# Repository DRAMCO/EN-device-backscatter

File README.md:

## Firmware

The firmware **firmware-vscode-exp-4b-part-2** is used in [experiment 4b](https://github.com/techtile-by-dramco/experiments/tree/main/04_backscatter_communication) part 2.

The firmware [**firmware-vscode-exp-4b-part-2-pseudorandom**](https://github.com/techtile-by-dramco/EN-device-backscatter/tree/main/firmware-vscode-exp-4b-part-2-pseudorandom) transmits 10 bytes preamble (0xAA) + 4096 bytes pseudo random code (baudrate 1000 bps) with a delay of 5 seconds between each transmission cycle.
One cycle requires 8 [bits/byte] * 1 [ms/bit] * (10 + 4096) [bytes] or in total 32.848 seconds.

## GNU Radio

The folder `gnuradio` contains the RX and TX files. The `receiver` folder contains `OOK.grc` to demodulate the modulated backscatter signal.

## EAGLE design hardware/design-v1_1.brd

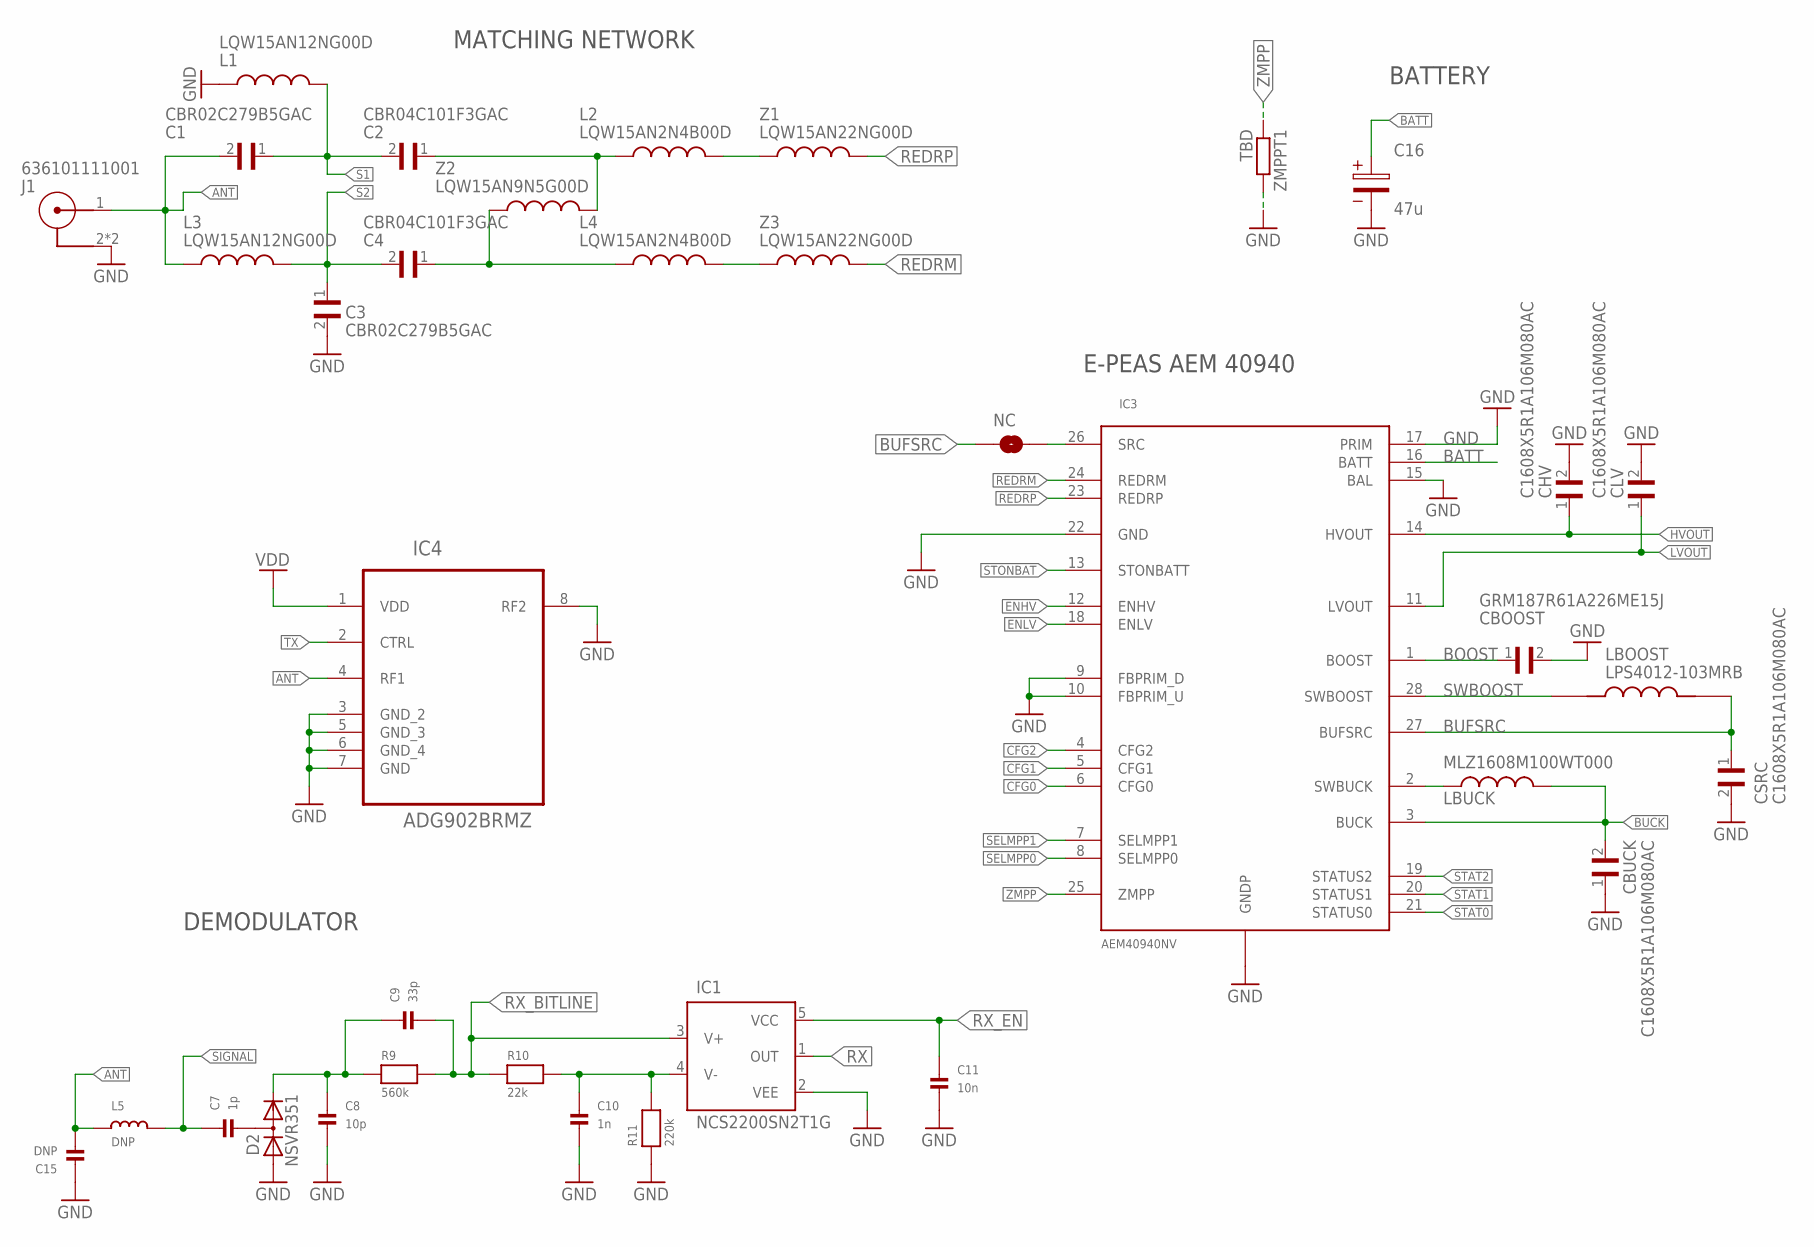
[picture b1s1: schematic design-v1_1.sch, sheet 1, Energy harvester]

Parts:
C1, C3: CBR02C279B5GAC; CAPC1005X55N
C2, C4: CBR04C101F3GAC; CAPC1005X55N
C7: 1p; 0402
C8: 10p; 0402
C9: 33p; 0402
C10: 1n; 0402
C11: 10n; 0402
C15: DNP; 0402
C16: 47u; 3X1.6X1.4(BXCXA)
CBOOST: GRM187R61A226ME15J; CAPC1608X80N
CBUCK: C1608X5R1A106M080AC; CAPC1608X90N
CHV: C1608X5R1A106M080AC; CAPC1608X90N
CLV: C1608X5R1A106M080AC; CAPC1608X90N
CSRC: C1608X5R1A106M080AC; CAPC1608X90N
D2: NSVR351; SOT23
IC1: NCS2200SN2T1G; SOT95P275X110-5N
IC3: AEM40940NV; QFN28_5X5_05P_NO_VIAS
IC4: ADG902BRMZ; SOP65P490X110-8N
J1: 636101111001
L1, L3: LQW15AN12NG00D; INDC1006X60N
L2, L4: LQW15AN2N4B00D; INDC1006X60N
L5: DNP; _0402
LBOOST: LPS4012-103MRB; IND_LPS4012-103MRB
LBUCK: MLZ1608M100WT000; INDC1608X95N
NC: JUMPER-SMT_2_NO_SILK; SMT-JUMPER_2_NO_SILK
R9: 560k; 0402
R10: 22k; 0402
R11: 220k; 0402
Z1, Z3: LQW15AN22NG00D; INDC1006X60N
Z2: LQW15AN9N5G00D; INDC1006X60N
ZMPPT1: TBD; R0805

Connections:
ANT: C1.2, C15.2, IC4.4 (RF1), J1.1, L3.1, L5.1
BATT: C16.1, IC3.16 (BATT); also elsewhere on the board
BOOST: CBOOST.1, IC3.1 (BOOST); also elsewhere on the board
BUCK: CBUCK.2, IC3.3 (BUCK), LBUCK.2; also elsewhere on the board
BUFSRC: CSRC.1, IC3.27 (BUFSRC), LBOOST.2, NC.2; also elsewhere on the board
CFG0: IC3.6 (CFG0); also elsewhere on the board
CFG1: IC3.5 (CFG1); also elsewhere on the board
CFG2: IC3.4 (CFG2); also elsewhere on the board
ENHV: IC3.12 (ENHV); also elsewhere on the board
ENLV: IC3.18 (ENLV); also elsewhere on the board
GND: C3.2, C8.2, C10.2, C11.2, C15.1, C16.2, CBOOST.2, CBUCK.1, CHV.2, CLV.2, CSRC.2, D2.1 (A), IC1.2 (VEE), IC3.9 (FBPRIM_D), IC3.10 (FBPRIM_U), IC3.15 (BAL), IC3.17 (PRIM), IC3.22 (GND), IC3.GND (GNDP), IC4.3 (GND_2), IC4.5 (GND_3), IC4.6 (GND_4), IC4.7 (GND), IC4.8 (RF2), J1.2, J1.3 (2), L1.1, R11.1, ZMPPT1.2; also elsewhere on the board
HVOUT: CHV.1, IC3.14 (HVOUT); also elsewhere on the board
LVOUT: CLV.1, IC3.11 (LVOUT); also elsewhere on the board
unnamed: C2.1, L2.1, Z2.2
unnamed: IC3.2 (SWBUCK), LBUCK.1
unnamed: C4.1, L4.1, Z2.1
unnamed: L2.2, Z1.1
unnamed: L4.2, Z3.1
unnamed: IC3.26 (SRC), NC.1
unnamed: C10.1, IC1.4 (V-), R10.2, R11.2
unnamed: C8.1, C9.1, D2.2 (C), R9.1
unnamed: C7.2, D2.3 (AC)
REDRM: IC3.24 (REDRM), Z3.2
REDRP: IC3.23 (REDRP), Z1.2
RX: IC1.1 (OUT); also elsewhere on the board
RX_BITLINE: C9.2, IC1.3 (V+), R9.2, R10.1
RX_EN: C11.1, IC1.5 (VCC); also elsewhere on the board
S1: C1.1, C2.2, L1.2; also elsewhere on the board
S2: C3.1, C4.2, L3.2; also elsewhere on the board
SELMPP0: IC3.8 (SELMPP0); also elsewhere on the board
SELMPP1: IC3.7 (SELMPP1); also elsewhere on the board
SIGNAL: C7.1, L5.2; also elsewhere on the board
STAT0: IC3.21 (STATUS0); also elsewhere on the board
STAT1: IC3.20 (STATUS1); also elsewhere on the board
STAT2: IC3.19 (STATUS2); also elsewhere on the board
STONBAT: IC3.13 (STONBATT); also elsewhere on the board
SWBOOST: IC3.28 (SWBOOST), LBOOST.1
TX: IC4.2 (CTRL); also elsewhere on the board
VDD: IC4.1 (VDD); also elsewhere on the board
ZMPP: IC3.25 (ZMPP), ZMPPT1.1

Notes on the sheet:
MATCHING NETWORK
E-PEAS AEM 40940
BATTERY
DEMODULATOR

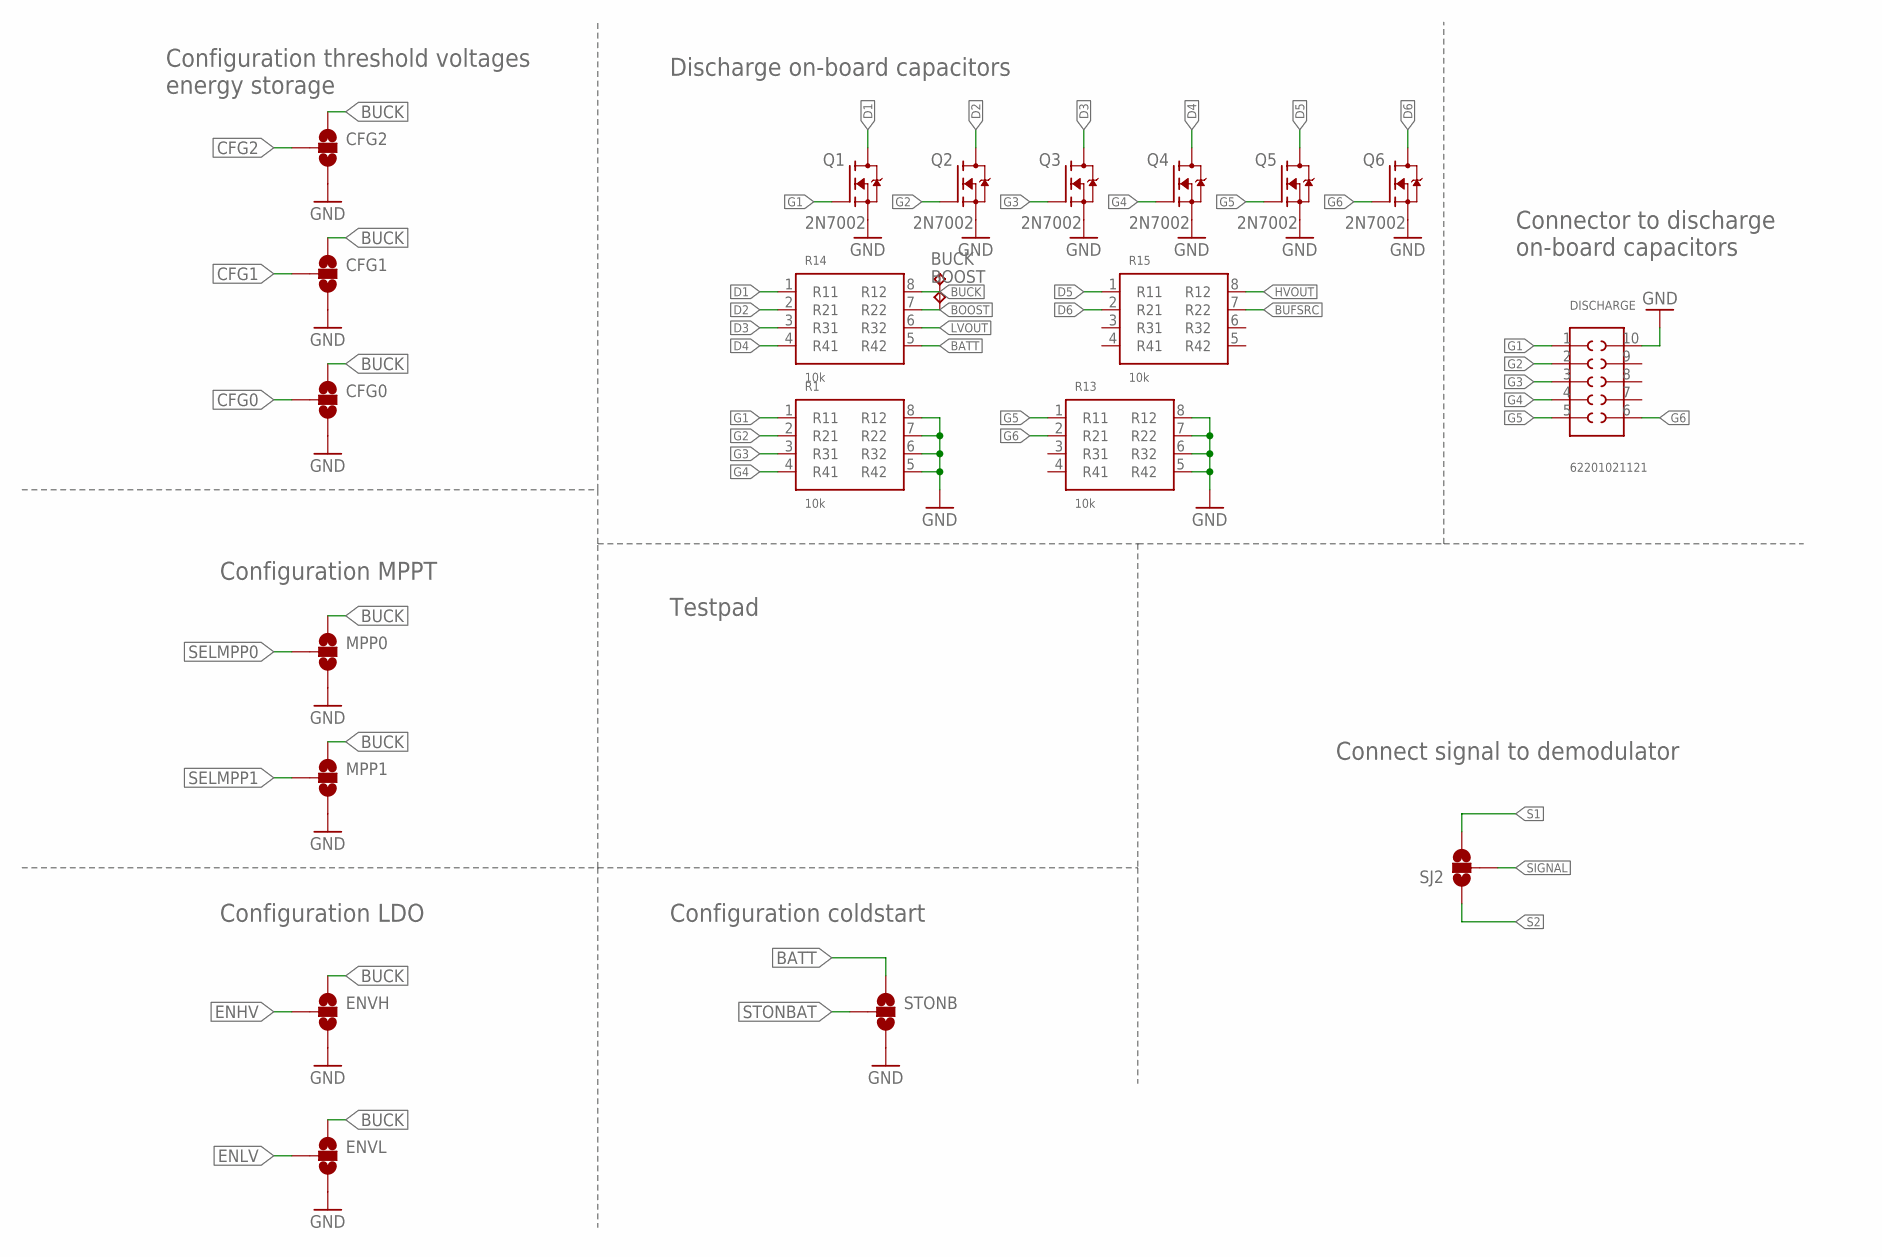
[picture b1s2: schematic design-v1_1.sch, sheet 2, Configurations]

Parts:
BOOST: TPTP06R; TP06R
BUCK: TPTP06R; TP06R
CFG0, CFG1, CFG2: JUMPER-SMT_3_NO_SILK; SMT-JUMPER_3_NO_SILK
DISCHARGE: 62201021121
ENVH: JUMPER-SMT_3_NO_SILK; SMT-JUMPER_3_NO_SILK
ENVL: JUMPER-SMT_3_NO_SILK; SMT-JUMPER_3_NO_SILK
MPP0, MPP1: JUMPER-SMT_3_NO_SILK; SMT-JUMPER_3_NO_SILK
Q1, Q2, Q3, Q4, Q5, Q6: 2N7002; SOT95P240X111-3N
R1, R13, R14, R15: 10k; RESCAXS50P200X100X45-8N
SJ2: SOLDERJUMPER_2WAYS; SJ_3
STONB: JUMPER-SMT_3_NO_SILK; SMT-JUMPER_3_NO_SILK

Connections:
BATT: R14.5 (R42), STONB.1; also elsewhere on the board
BOOST: BOOST.TP, R14.7 (R22); also elsewhere on the board
BUCK: BUCK.TP, CFG0.1, CFG1.1, CFG2.1, ENVH.1, ENVL.1, MPP0.1, MPP1.1, R14.8 (R12); also elsewhere on the board
BUFSRC: R15.7 (R22); also elsewhere on the board
CFG0: CFG0.2; also elsewhere on the board
CFG1: CFG1.2; also elsewhere on the board
CFG2: CFG2.2; also elsewhere on the board
D1: Q1.3 (D), R14.1 (R11)
D2: Q2.3 (D), R14.2 (R21)
D3: Q3.3 (D), R14.3 (R31)
D4: Q4.3 (D), R14.4 (R41)
D5: Q5.3 (D), R15.1 (R11)
D6: Q6.3 (D), R15.2 (R21)
ENHV: ENVH.2; also elsewhere on the board
ENLV: ENVL.2; also elsewhere on the board
G1: DISCHARGE.1, Q1.1 (G), R1.1 (R11)
G2: DISCHARGE.2, Q2.1 (G), R1.2 (R21)
G3: DISCHARGE.3, Q3.1 (G), R1.3 (R31)
G4: DISCHARGE.4, Q4.1 (G), R1.4 (R41)
G5: DISCHARGE.5, Q5.1 (G), R13.1 (R11)
G6: DISCHARGE.6, Q6.1 (G), R13.2 (R21)
GND: CFG0.3, CFG1.3, CFG2.3, DISCHARGE.10, ENVH.3, ENVL.3, MPP0.3, MPP1.3, Q1.2 (S), Q2.2 (S), Q3.2 (S), Q4.2 (S), Q5.2 (S), Q6.2 (S), R1.5 (R42), R1.6 (R32), R1.7 (R22), R1.8 (R12), R13.5 (R42), R13.6 (R32), R13.7 (R22), R13.8 (R12), STONB.3; also elsewhere on the board
HVOUT: R15.8 (R12); also elsewhere on the board
LVOUT: R14.6 (R32); also elsewhere on the board
S1: SJ2.3; also elsewhere on the board
S2: SJ2.1; also elsewhere on the board
SELMPP0: MPP0.2; also elsewhere on the board
SELMPP1: MPP1.2; also elsewhere on the board
SIGNAL: SJ2.2; also elsewhere on the board
STONBAT: STONB.2; also elsewhere on the board

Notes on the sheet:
Configuration threshold voltages energy storage
Configuration MPPT
Configuration LDO
Configuration coldstart
Testpad
Discharge on-board capacitors
Connector to discharge on-board capacitors
Connect signal to demodulator

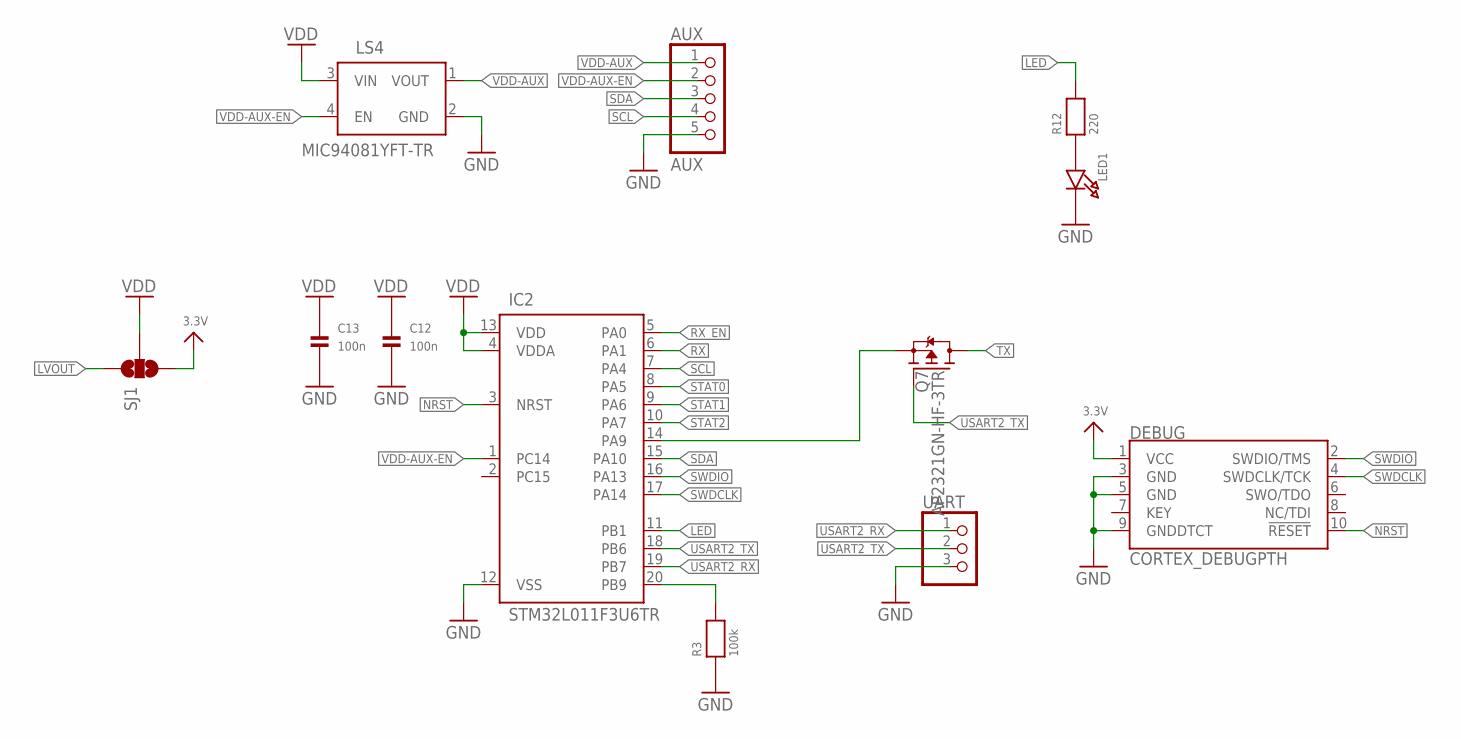
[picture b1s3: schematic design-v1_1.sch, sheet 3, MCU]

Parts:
AUX: AUX; 1X05_ROUND
C12, C13: 100n; 0402
DEBUG: CORTEX_DEBUGPTH; 2X5-PTH-1.27MM
IC2: STM32L011F3U6TR; QFN50P300X300X60-21N
LED1: LED0805; CHIPLED_0805
LS4: MIC94081YFT-TR; IC_MIC94081YFT-TR
Q7: AP2321GN-HF-3TR; SOT23-3
R3: 100k; 0402
R12: 220; 0603
SJ1: SOLDERJUMPER_2WAYS; SJ_3
UART: HEADER-1X3ROUND; 1X03_ROUND

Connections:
3.3V: DEBUG.1 (VCC), SJ1.3
GND: AUX.5, C12.2, C13.2, DEBUG.3 (GND), DEBUG.5 (GND), DEBUG.9 (GNDDTCT), IC2.12 (VSS), LED1.C, LS4.2 (GND), R3.1, UART.3; also elsewhere on the board
LED: IC2.11 (PB1), R12.2
LVOUT: SJ1.1; also elsewhere on the board
unnamed: IC2.14 (PA9), Q7.2 (S)
unnamed: LED1.A, R12.1
NRST: DEBUG.10 (!RESET), IC2.3 (NRST)
PB9: IC2.20 (PB9), R3.2
RX: IC2.6 (PA1); also elsewhere on the board
RX_EN: IC2.5 (PA0); also elsewhere on the board
SCL: AUX.4, IC2.7 (PA4)
SDA: AUX.3, IC2.15 (PA10)
STAT0: IC2.8 (PA5); also elsewhere on the board
STAT1: IC2.9 (PA6); also elsewhere on the board
STAT2: IC2.10 (PA7); also elsewhere on the board
SWDCLK: DEBUG.4 (SWDCLK/TCK), IC2.17 (PA14)
SWDIO: DEBUG.2 (SWDIO/TMS), IC2.16 (PA13)
TX: Q7.3 (D); also elsewhere on the board
USART2_RX: IC2.19 (PB7), UART.1
USART2_TX: IC2.18 (PB6), Q7.1 (G), UART.2
VDD: C12.1, C13.1, IC2.4 (VDDA), IC2.13 (VDD), LS4.3 (VIN), SJ1.2; also elsewhere on the board
VDD-AUX: AUX.1, LS4.1 (VOUT)
VDD-AUX-EN: AUX.2, IC2.1 (PC14), LS4.4 (EN)

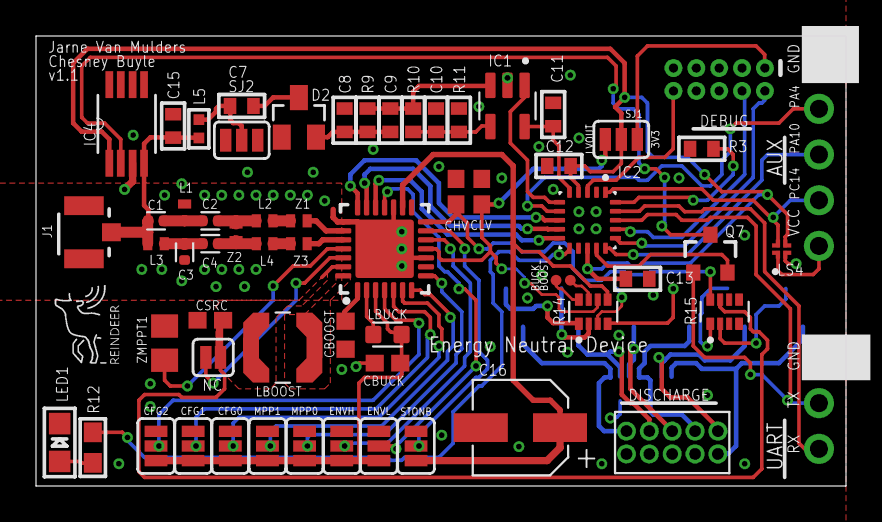
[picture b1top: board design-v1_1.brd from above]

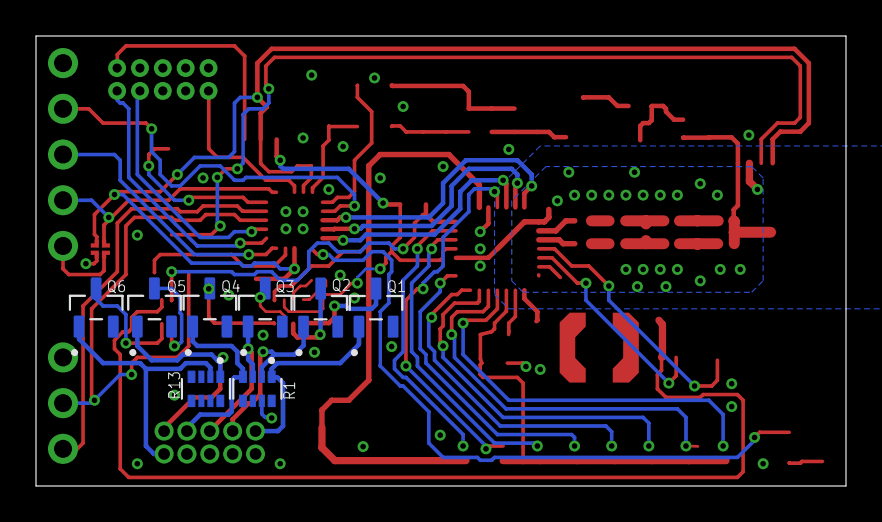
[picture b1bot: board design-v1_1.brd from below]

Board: 2 copper layers, 45.0 x 25.0 mm, 70 parts (8 on the bottom side), 66 nets.

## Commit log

2022-12-23 Add modulation library
2023-01-03 Structured + added GRC files for OOK demodulation
2023-05-19 Add hardware folder and CAD files
2023-12-13 Firmware update (vscode IDE compatible)
    "tx_byte()" command to backscatter bytes.
    Internal circular buffer to store bytes and send them sequentially.
2023-12-13 Update tx frame format (first demodulation tests)
2024-03-19 Firmware updates
2024-04-29 Add new firmware (exp 4b part 2)
2024-05-21 Added demod and testfile
2024-06-25 New pseudo random code firmware

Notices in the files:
parts and their libraries:
SparkFun-Jumpers: Licensing: Creative Commons ShareAlike 4.0 International - https://creativecommons.org/licenses/by-sa/4.0
Eagle_WR-UMRF: Copyright: Würth Elektronik
supply0: Copyright (C) 2007, Bob Starr
